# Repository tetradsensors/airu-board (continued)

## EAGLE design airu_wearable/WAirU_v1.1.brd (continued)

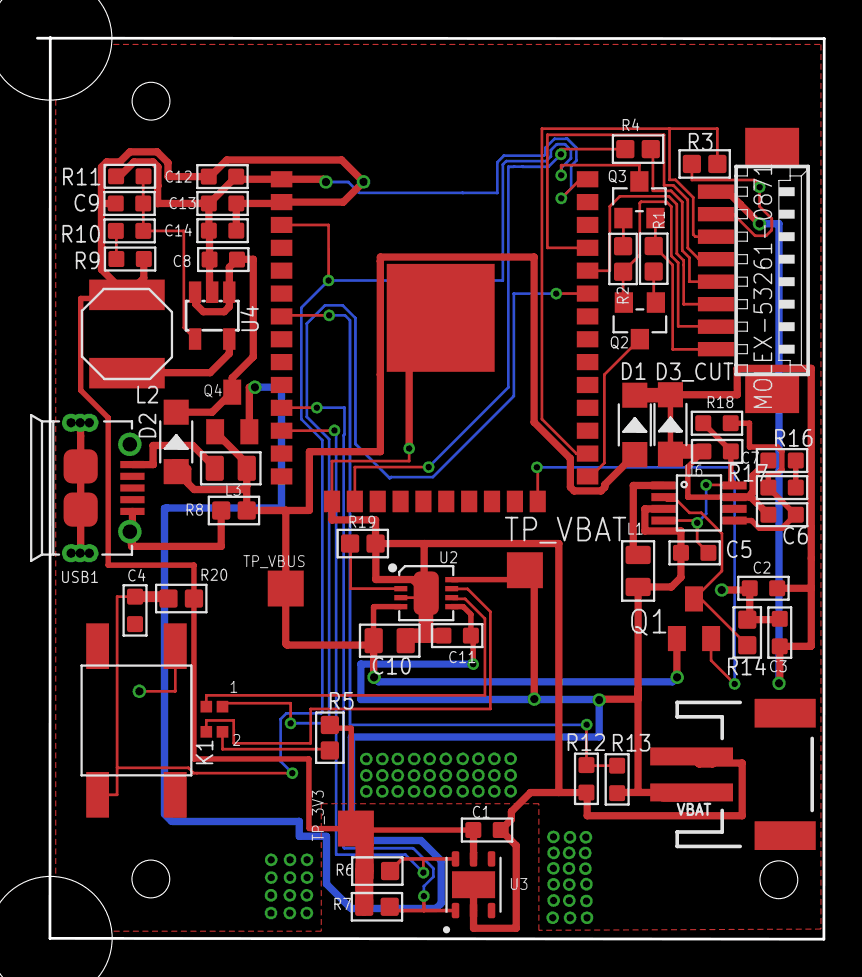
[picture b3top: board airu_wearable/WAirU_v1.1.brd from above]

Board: 2 copper layers, 43.7 x 50.1 mm, 56 parts (0 on the bottom side), 35 nets.

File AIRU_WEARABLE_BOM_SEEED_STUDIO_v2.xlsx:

Designator | MPN/Seeed SKU | Qty | Value | Device | Package | MPN
5.0V1, TP_3V3, TP_VBAT, TP_VIN1 | Test pad | 4 | TPTP20SQ | TPTP20SQ | TP20SQ
C1, C3, C4 | 302010139 | 3 | 1uf | CERAMIC-1UF-25V-10%-X7R(0603) | C0603 | CC0603KRX7R8BB105
C11 | 302010111 | 1 | 4.7uf | CERAMIC-4.7UF-10V-10%-X5R(0603) | C0603 | CC0603KRX5R6BB475
C2 | 302010138 | 1 | 100nf | CERAMIC-100NF-50V-10%-X7R(0603) | C0603 | CC0603KRX7R9BB104
C5, C8, C10, C12, C13, C14 | 302010103 | 6 | 10uf | CERAMIC-10UF-10V-10%-X5R(0603) | C0603 | CC0603KRX5R6BB106
C6, C7 | 302010103 | 2 | 22uf | CERAMIC-10UF-10V-10%-X5R(0603) | C0603 | CC0603KRX5R6BB106
C9 | 302010076 | 1 | 100pf | CERAMIC-100PF-50V-5%-NPO(0603) | C0603 | CC0603JRNPO9BN101
D1, D2 | 304020034 | 2 | 20V-1A | SMD-DIODE-SCHOTTKY-20V-1A(SOD-123) | SOD-123 | B5819W
K1 | 311020004 | 1 |  | SMD-SWITCH-TACTILE-SPST-NO(4P-D6.0MM) | SW4-SMD-6.0X6.0X5.0MM | DTSM-62K-S-V-T/R(SN431)
L1 | 303010086 | 1 | 2.2UH-1.2A | SMD-INDUCTOR-2.2UH-20%-1.2A(0805) | L0805 | LQM2MPN2R2MG0
L2 | 303010147 | 1 | 4.7uH | SMD-INDUCTOR-10UH-20%-2.35A(2P-5X5X4MM) | L5040S
L3 | 303030006 | 1 | 330R-1500MA | SMD-FERRITE-BEAD-330R-1500MA(0805)'0805' | L0805 | BLM21PG331SN1D
MOLEX-53261-0871 | CONNECTOR | 1 | 53261-08 | 53261-08 | 53261-08
Q1 | N-CHANNEL MOS FET | 1 | BSS123 | BSS123 | SOT23
Q2, Q3 | 305010013 | 2 | MMBT3904LT1G | SMD-TRANSISTORS-NPN-40V-200MA-MMBT3904LT1G(SOT-23) | SOT-23 | MMBT3904LT1G
Q4 | P-CHANNEL MOS FET | 1 | BSS84 | BSS84 | SOT23
R1, R2, R20 | 301010299 | 3 | 10K | SMD-RES-10K-1%-1/10W(0603) | R0603 | RC0603FR-0710KL
R10, R17 | 301010177 | 2 | 69.8K 1/10W | SMD-RES-69.8K-1%-1/10W(0603) | R0603 | RC0603FR-0769K8L
R11 | 301010217 | 1 | 120K | SMD-RES-120K-1%-1/10W(0603) | R0603 | RC0603FR-07120KL
R16 | 301010246 | 1 | 680K | SMD-RES-680K-1%-1/16W(0603) | R0603 | RC0603FR-07680KL
R19 | 301010198 | 1 | 6.8K | SMD-RES-6.8K-1%-1/10W(0603) | R0603 | RC0805JR-07220KL
R3 | 301010163 | 1 | 4.7K | SMD-RES-220R-5%-1/10W(0603) | R0603 | RC0603JR-07220RL
R4 | 301010163 | 1 | 220R | SMD-RES-220R-5%-1/10W(0603) | R0603 | RC0603JR-07220RL
R5 | 301010300 | 1 | 330R | SMD-RES-330R-1%-1/10W(0603) | R0603 | RC0603FR-07330RL
R6, R7 | 301010290 | 2 | 4.7K | SMD-RES-4.7K-5%-1/10W(0603) | R0603 | RC0603JR-074K7L
R8, R12, R13, R14, R15, R18 | 301011975 | 6 | 100K 1/10W | SMD-RES-100K-5%-1/10W(0603) | R0603 | RC0603JR-07100KL
R9 | 301010190 | 1 | 470K | SMD-RES-470K-1%-1/10W(0603) | R0603 | RC0603FR-07470KL
U1 | 19-237A/BHR6GHC-M01/2T | 1 | 19-237A/BHR6GHC-M01/2T | 19-237A/BHR6GHC-M01/2T | SMD-19-237A
U2 | 310030101 | 1 | CN3065-DFN8 | PMIC-CN3065(DFN8) | DFN8G-0.5-3X3MM | CN3065
U3 | HDC1080 Low Power, High Accuracy Digital Humidity Sensor with Temperature Senso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 | 1 | HDC1080DMBT | HDC1080DMBT | SON100P300X300X80-7N
U4 | 310030033 | 1 | PAM2305AABADJ | PMIC-LP2985-33DBVR(SOT23-5) | SOT-23-5 | LP2985-33DBVR
U6 | PAM2401SCADJ | 1 | PAM2401SCADJ | PAM2401 | MSOP-8 | PAM2401SCADJ
U7 | ESP32-WROOM-32 | 1 | ESP32_WROOM32_SKINNY | ESP32_WROOM32_SKINNY | WROOM32_SKINNY
USB1 | 320010005 | 1 | ZX62-B-5PA | MICRO-USB-SMD(ZX62-B-5PA) | MICRO-USB5+6P-SMD-0.65-AB | ZX62-B-5PA
VBAT | Multi connection point. Often used as Generic Header-pin footprint for 0.1 inch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 | 1 |  | CONN_02-JST-2MM-SMT | JST-2-SMD

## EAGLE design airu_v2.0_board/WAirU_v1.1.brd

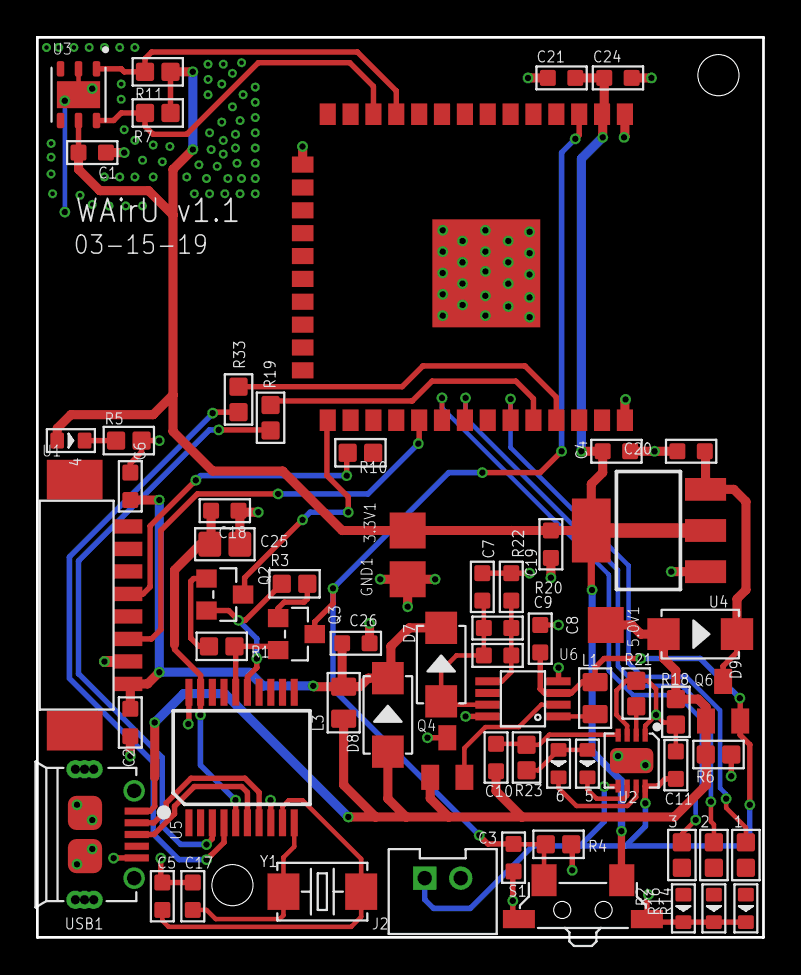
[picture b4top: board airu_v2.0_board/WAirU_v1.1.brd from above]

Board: 2 copper layers, 40.3 x 50.0 mm, 66 parts (0 on the bottom side), 41 nets.

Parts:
1, 6: RED-0603; LED-0603
2, 5: GREEN-0603; LED-0603
3: BLUE-0603; LED-0603
3.3V1, 5.0V1: TPTP20SQ; TP20SQ
4: YELLOW-0603; LED-0603
C1, C3, C4, C6: 1uf; C0603
C2, C18: 100nf; C0603
C5, C17: 22pf; C0603
C7, C9, C10: 22uf; C0603
C8, C19, C20, C21, C24, C26: 10uf; C0603
C11: 4.7uf; C0603
C25: 22uf; C0805
D7, D8, D9: 40V-1A; DO-214AC
GND1: TPTP20SQ; TP20SQ
J2: 2p-2.0; H2-2.0-6X4.5MM
L1: 2.2UH-1.2A; L0805
L3: 330R-1500MA; L0805
Q2, Q3: MMBT3904LT1G; SOT-23
Q4, Q6: BSS84; SOT23
R1, R3, R4, R18: 10K; R0603
R2: 100R; R0603
R5, R10, R14, R19, R33: 220R; R0603
R6: 100K 1/10W; R0603
R7, R11: 4.7K; R0603
R16: 10R; R0603
R20: 750K; R0603
R21: 6.8K; R0603
R22: 100K; R0603
R23: 330R; R0603
S1: TS-1188E; SW4-SMD-7.0X3.5X3.5MM-90D
U1: MOLEX-53261-0871
U2: CN3065-DFN8; DFN8G-0.5-3X3MM
U3: HDC1080DMBT; SON100P300X300X80-7N
U4: CJT1117-3.3-SOT223; SOT-223
U5: CH340T-SSOP20; SSOP20-0.65-7.6X5.2MM
U6: PAM2401; MSOP-8
U7: ESP32_WROOM32_SKINNY; WROOM32_SKINNY
USB1: ZX62-B-5PA; MICRO-USB5+6P-SMD-0.65-AB
Y1: 12MHZ; X2-SMD-5.0X3.2X1.3MM

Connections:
3.3V: 3.3V1.TP, 4.+, C1.2, C4.2, C18.2, C19.2, C21.2, C24.2, C25.1, R7.2, R11.2, S1.2, U3.5, U4.2, U4.TER, U5.5, U5.19, U7.2
5.0V: C2.2, C6.2, C26.2, D7.2, D8.2, L3.2, U1.5V
DTR: Q2.2, R3.1, U5.15
GND: 1.-, 2.-, 3.-, C1.1, C2.1, C3.1, C4.1, C5.1, C6.1, C7.1, C8.1, C11.1, C17.1, C18.1, C19.1, C20.1, C21.1, C24.1, C25.2, C26.1, GND1.TP, J2.-, Q4.3, R4.1, R5.1, R6.1, R18.1, R21.1, R22.1, S1.S1, S1.S2, U1.GND, U2.1, U2.3, U2.HEAT, U3.2, U3.7, U4.1, U5.8, U5.20, U6.4, U6.8, U7.1, U7.15, U7.38, U7.P$1, USB1.5, USB1.P1, USB1.P2, USB1.P3_1, USB1.P3_2, USB1.P3_3, USB1.P4_1, USB1.P4_2, USB1.P4_3, USB1.P5, USB1.P6
GPIO0: Q2.3, U7.25
unnamed: 2.+, R16.1
unnamed: L1.2, U6.1
unnamed: Q4.2, U6.2
unnamed: C10.1, R23.2, U2.4
unnamed: R21.2, U2.2
unnamed: 1.+, R14.1
unnamed: C20.2, D9.2, Q6.3, U4.3
unnamed: C7.2, C9.2, D7.1, R20.2, U6.7
unnamed: C9.1, R20.1, R22.2, U6.5
unnamed: 5.+, 6.+, R23.1
unnamed: Q3.1, R3.2
unnamed: Q2.1, R1.2
unnamed: 5.-, U2.6
unnamed: R10.2, U1.TXD
unnamed: 4.-, R5.2
unnamed: 3.+, R2.1
unnamed: 6.-, U2.7
unnamed: U5.7, USB1.2
unnamed: U5.6, USB1.3
unnamed: C5.2, U5.9, Y1.2
unnamed: C17.2, U5.10, Y1.1
unnamed: R19.2, U5.3
unnamed: R33.2, U7.35
PM_SET: U1.SET, U7.29
RESET: C3.2, Q3.3, R4.2, S1.1, U7.3
RTS: Q3.2, R1.1, U5.16
RXD0: R19.1, U7.34
SCL: R7.1, U3.6, U7.12
SDA: R11.1, U3.1, U7.11
STAT_LED1: R14.2, U7.33
STAT_LED2: R16.2, U7.31
STAT_LED3: R2.2, U7.30
TXD0: R33.1, U5.4
U2RXD: R10.1, U7.27
VBAT: C8.2, C11.2, J2.+, L1.1, Q6.2, U2.5, U2.8, U6.3
VBUS: 5.0V1.TP, C10.2, D8.1, D9.1, L3.1, Q4.1, Q6.1, R6.2, R18.2, USB1.1

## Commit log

2019-04-26 updated board files to one-sided board
2019-04-26 removed awesome graphic
2019-04-26 added keepout on temperature sensor
2019-04-29 renamed project
2019-04-29 updated wearable
2019-04-29 updated V2
2019-05-09 Remove USB-TTL chip, flashing uses PM port, re-arrange according to Housing_bottomV1
2019-05-09 changed PM_SET to GPIO4
2019-05-09 routed PM_RESET and added dimensions, removed GND polygon from upper left
2019-05-09 - Remove led - Re-position Status Led 1 near the button - Replace reset button with SMD one - Route GND signal to ground plan - Add heat dissipation surrounding the temperature sensor - Remove ground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
2019-05-09 removed ground traces and added ground poly pour on top layer
2019-05-09 Change regulator, add rules for pads and vias, update new component to BOM sheet
2019-05-09 Pull down PM_SET and PM_RESET
2019-05-10 added .gitignore
2019-05-10 replaced LEDs with single LED, 5V and 3.3V buck/boost are now on the same VIN
2019-05-10 an airwire
2019-05-10 Apply changes in schematic to PCB
2019-05-10 Add BOM file for wearable
2019-05-10 updated BoM
2019-05-10 removed old directories
2019-05-14 made holes smaller
2019-05-14 removed old files
2019-05-14 Move battery header on to board
2019-05-14 Adjusted the battery connector away from mounting hole
2019-05-14 no change
2019-09-11 updated to v2.1
2019-09-11 .gitignore fix
2019-09-11 changed eagle dir name
2019-09-11 reorganizing
2019-09-11 gitignore fix
2019-09-19 added pdf.
2019-09-30 Remove pull down on PM_SET line
2019-09-30 Fix Schematic for #9, #10, #11, #12 on github opening issue
2019-10-22 Added Switch circuit PAM2401 input for VBUS and VBAT. Added voltage divider for PAM2401 output
2019-10-23 100kOhm PD on Q1 Removed D1 C10 decoupling grounded PMRST to GPIO2 U2RXD to GPIO13
2019-10-23 Add BOM file and printed schematic file for this major update
2019-10-25 PCB design
2019-10-30 new issue (#16) opened. Remade PAM2401 circuit.
2019-10-30 added comment.
2019-10-30 re-arrange pcb
2019-10-30 Added PoE components
2019-10-31 Draw PCB plus dimension for WAirU 2.1 Export BOM list Included PCB pdf for future references
2019-11-03 Adjust PCB dimensions to 43x50 to fit with PMS3003. Remove corner, radius 3.5mm
2019-11-06 Added corner peck holes. Adjusted position of items: button, USB header. Removed VBAT and D3_CUT from BOM
2019-11-11 fixed AG9900M pins
2019-11-19 update BOM for wearable. Added mouser link for 8 pin connector and humidity sensor
2019-11-20 added graphic
2019-11-20 add picture
2019-11-20 added dimensions from Michael.
2019-12-09 Added pin description for rgb LED U1
2020-04-26 update 2020
2020-04-26 remove V1 files
2020-04-26 add proto files
2020-04-26 update BOM
2020-07-23 removed airu logo
    also updated version text
2020-07-23 board update
    PM SET/RESET moved to RTC GPIO pins, MiCS pins swapped to avoid cross-over, sd moved to bottom, usb-uart moved to bottom, gps moved, temp sensor moved to avoid overheating, 5v-3.3v converter moved, 3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
2020-07-24 updated board
    changed PM_RESET to an RTC GPIO (previously unpopulated), and changed the logo/revision info
2020-07-24 updated names
